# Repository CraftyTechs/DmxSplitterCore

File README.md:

DmxSplitterCore
===============

Core module of DMX splitter. Excludes '485 drivers, front panel controls and power supply.

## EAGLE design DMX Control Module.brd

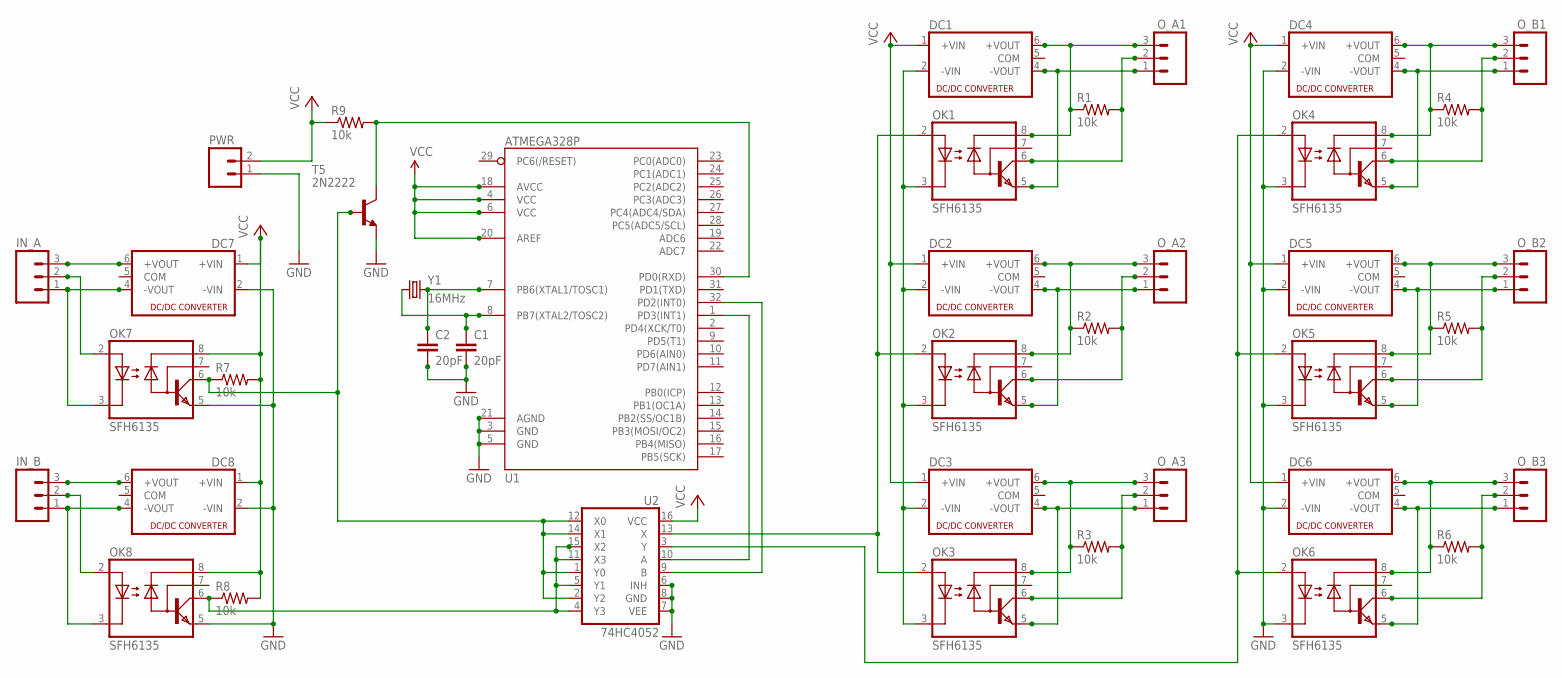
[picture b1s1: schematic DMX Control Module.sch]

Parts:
C1, C2: 20pF; CAP-PTH-SMALL
DC1, DC2, DC3, DC4, DC5, DC6, DC7, DC8: NMA
IN_A: M03PTH; 1X03
IN_B: M03PTH; 1X03
OK1, OK2, OK3, OK4, OK5, OK6, OK7, OK8: SFH6135; DIL08
O_A1, O_A2, O_A3: M03PTH; 1X03
O_B1, O_B2, O_B3: M03PTH; 1X03
PWR: M02PTH; 1X02
R1, R2, R3, R4, R5, R6, R7, R8, R9: 10k; AXIAL-0.4
T5: 2N2222; TO92
U1: ATMEGA328P; TQFP32-08
U2: 74HC4052; DIL16
Y1: 16MHz; HC49US

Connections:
GND: C1.2, C2.2, DC4.2 (-VIN), DC5.2 (-VIN), DC6.2 (-VIN), DC7.2 (-VIN), DC8.2 (-VIN), OK4.3 (C), OK5.3 (C), OK6.3 (C), OK7.5 (GND), OK8.5 (GND), PWR.1, T5.1 (E), U1.3 (GND), U1.5 (GND), U1.21 (AGND), U2.6 (INH), U2.7 (VEE), U2.8 (GND)
unnamed: C2.1, U1.7 (PB6(XTAL1/TOSC1)), Y1.2
unnamed: C1.1, U1.8 (PB7(XTAL2/TOSC2)), Y1.1
unnamed: DC1.6 (+VOUT), OK1.8 (VCC), O_A1.3, R1.P$1 (1)
unnamed: DC1.4 (-VOUT), OK1.5 (GND), O_A1.1
unnamed: OK1.6 (VO), O_A1.2, R1.P$2 (2)
unnamed: DC2.6 (+VOUT), OK2.8 (VCC), O_A2.3, R2.P$1 (1)
unnamed: DC2.4 (-VOUT), OK2.5 (GND), O_A2.1
unnamed: OK2.6 (VO), O_A2.2, R2.P$2 (2)
unnamed: DC3.6 (+VOUT), OK3.8 (VCC), O_A3.3, R3.P$1 (1)
unnamed: DC3.4 (-VOUT), OK3.5 (GND), O_A3.1
unnamed: OK3.6 (VO), O_A3.2, R3.P$2 (2)
unnamed: DC4.6 (+VOUT), OK4.8 (VCC), O_B1.3, R4.P$1 (1)
unnamed: DC4.4 (-VOUT), OK4.5 (GND), O_B1.1
unnamed: OK4.6 (VO), O_B1.2, R4.P$2 (2)
unnamed: OK7.6 (VO), R7.P$1 (1), T5.2 (B), U2.1 (Y0), U2.2 (Y2), U2.12 (X0), U2.14 (X1)
unnamed: DC5.4 (-VOUT), OK5.5 (GND), O_B2.1
unnamed: OK5.6 (VO), O_B2.2, R5.P$2 (2)
unnamed: DC6.6 (+VOUT), OK6.8 (VCC), O_B3.3, R6.P$1 (1)
unnamed: DC6.4 (-VOUT), OK6.5 (GND), O_B3.1
unnamed: OK6.6 (VO), O_B3.2, R6.P$2 (2)
unnamed: DC1.2 (-VIN), DC2.2 (-VIN), DC3.2 (-VIN), OK1.3 (C), OK2.3 (C), OK3.3 (C)
unnamed: OK8.6 (VO), R8.P$1 (1), U2.4 (Y3), U2.5 (Y1), U2.11 (X3), U2.15 (X2)
unnamed: U1.32 (PD2(INT0)), U2.9 (B)
unnamed: U1.1 (PD3(INT1)), U2.10 (A)
unnamed: DC7.6 (+VOUT), IN_A.3
unnamed: DC7.4 (-VOUT), IN_A.1, OK7.3 (C)
unnamed: IN_A.2, OK7.2 (A)
unnamed: DC8.6 (+VOUT), IN_B.3
unnamed: DC8.4 (-VOUT), IN_B.1, OK8.3 (C)
unnamed: IN_B.2, OK8.2 (A)
unnamed: R9.P$2 (2), T5.3 (C), U1.30 (PD0(RXD))
unnamed: OK1.2 (A), OK2.2 (A), OK3.2 (A), U2.13 (X)
unnamed: OK4.2 (A), OK5.2 (A), OK6.2 (A), U2.3 (Y)
O_B2: DC5.6 (+VOUT), OK5.8 (VCC), O_B2.3, R5.P$1 (1)
VCC: DC1.1 (+VIN), DC2.1 (+VIN), DC3.1 (+VIN), DC4.1 (+VIN), DC5.1 (+VIN), DC6.1 (+VIN), DC7.1 (+VIN), DC8.1 (+VIN), OK7.8 (VCC), OK8.8 (VCC), PWR.2, R7.P$2 (2), R8.P$2 (2), R9.P$1 (1), U1.4 (VCC), U1.6 (VCC), U1.18 (AVCC), U1.20 (AREF), U2.16 (VCC)

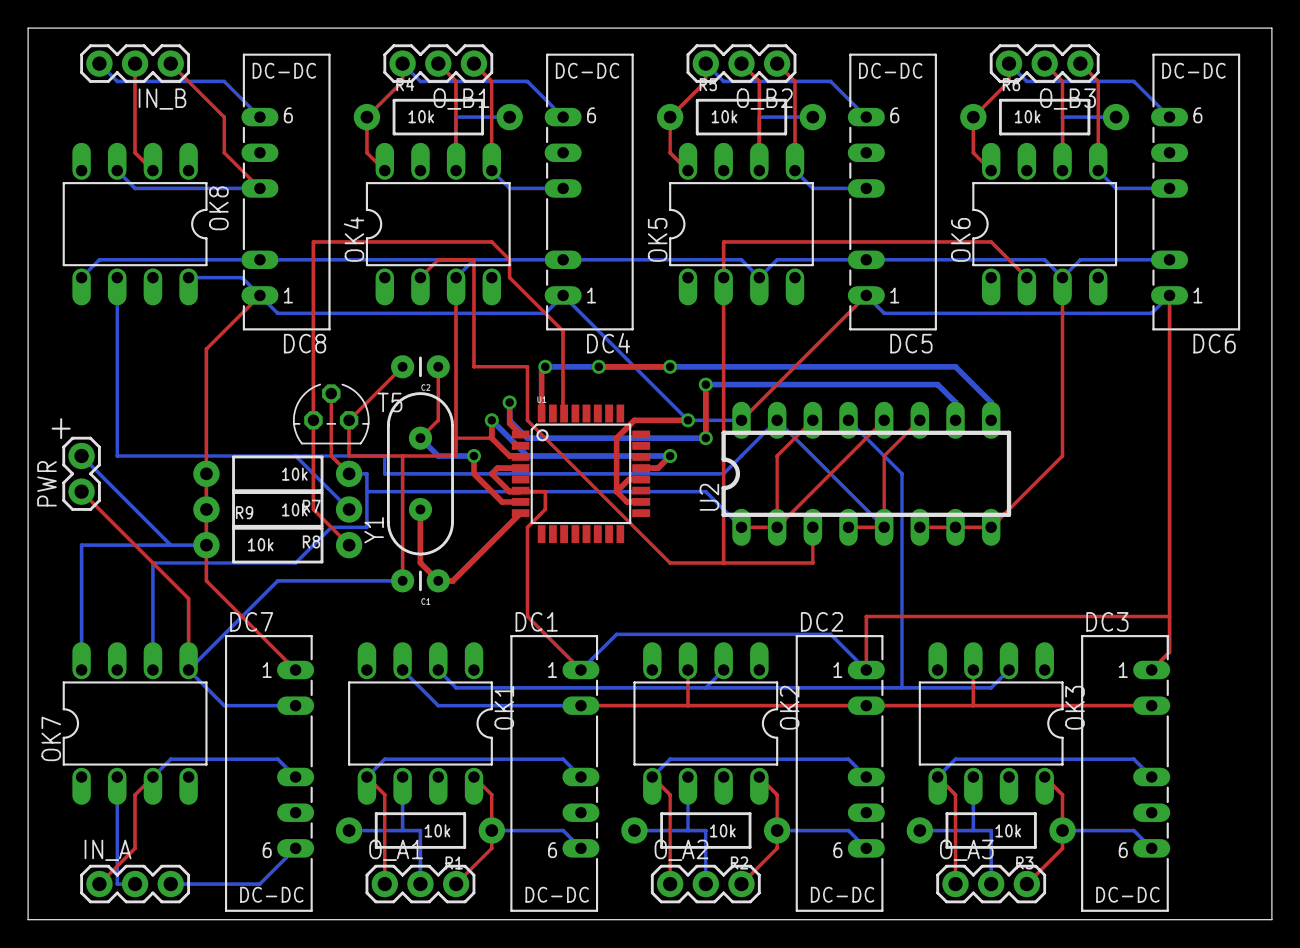
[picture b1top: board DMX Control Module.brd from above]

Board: 2 copper layers, 88.6 x 63.5 mm, 40 parts (0 on the bottom side), 36 nets.

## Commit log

2014-05-28 Initial commit of Eagle files

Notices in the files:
parts and their libraries:
SparkFun-DigitalIC: Licensing: Creative Commons ShareAlike 4.0 International - https://creativecommons.org/licenses/by-sa/4.0
